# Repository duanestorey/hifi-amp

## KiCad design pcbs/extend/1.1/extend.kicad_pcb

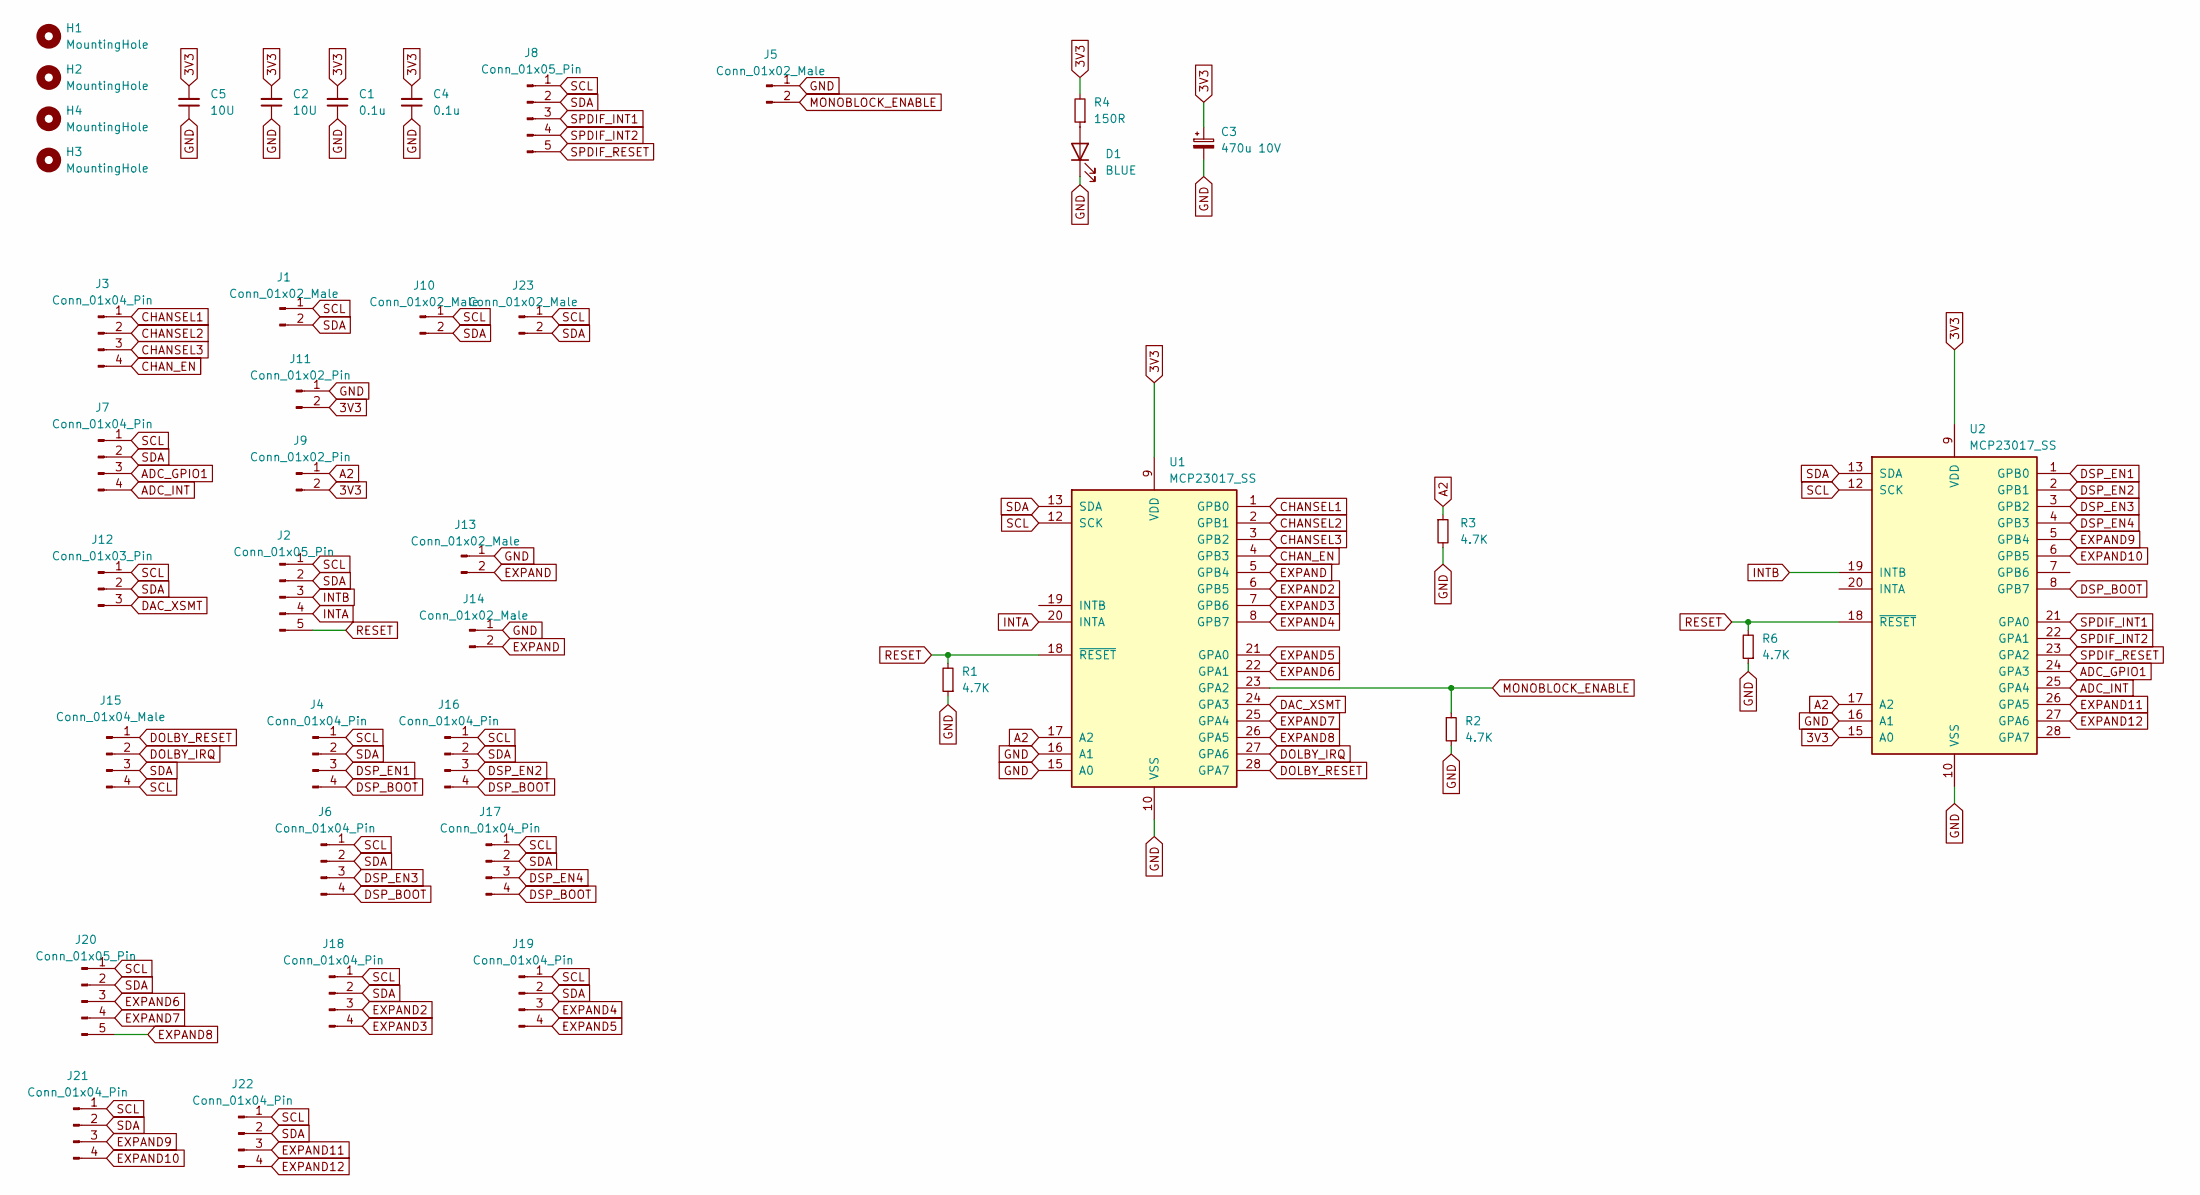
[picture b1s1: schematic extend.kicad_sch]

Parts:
C1, C4: 0.1u; C_0805_2012Metric_Pad1.18x1.45mm_HandSolder
C2, C5: 10U; C_1206_3216Metric_Pad1.33x1.80mm_HandSolder
C3: 470u 10V; CP_Radial_D6.3mm_P2.50mm
D1: BLUE; LED_0603_1608Metric
H1, H2, H3, H4: MountingHole; MountingHole_3.2mm_M3_DIN965_Pad_TopOnly
J1, J5, J10, J13, J23: Conn_01x02_Male; JST_PH_B2B-PH-K_1x02_P2.00mm_Vertical
J2, J8, J20: Conn_01x05_Pin; JST_PH_B5B-PH-K_1x05_P2.00mm_Vertical
J3, J4, J6, J7, J16, J17, J18, J19, J21, J22: Conn_01x04_Pin; JST_PH_B4B-PH-K_1x04_P2.00mm_Vertical
J9: Conn_01x02_Pin; PinHeader_1x02_P2.54mm_Vertical
J11: Conn_01x02_Pin; JST_PH_B2B-PH-K_1x02_P2.00mm_Vertical
J12: Conn_01x03_Pin; JST_PH_B3B-PH-K_1x03_P2.00mm_Vertical
J14: Conn_01x02_Male; PinHeader_1x02_P2.54mm_Vertical
J15: Conn_01x04_Male; JST_PH_B4B-PH-K_1x04_P2.00mm_Vertical
R1, R2, R3, R6: 4.7K; R_0603_1608Metric_Pad0.98x0.95mm_HandSolder
R4: 150R; R_0603_1608Metric
U1, U2: MCP23017_SS; SSOP-28_5.3x10.2mm_P0.65mm; Mouser 579-MCP23017-E/SS

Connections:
3V3: C1.2, C2.2, C3.1, C4.2, C5.2, J9.2, J11.2, R4.2, U1.9 (VDD), U2.9 (VDD), U2.15 (A0)
A2: J9.1, R3.1, U1.17 (A2), U2.17 (A2)
ADC_GPIO1: J7.3, U2.24 (GPA3)
ADC_INT: J7.4, U2.25 (GPA4)
CHANSEL1: J3.1, U1.1 (GPB0)
CHANSEL2: J3.2, U1.2 (GPB1)
CHANSEL3: J3.3, U1.3 (GPB2)
CHAN_EN: J3.4, U1.4 (GPB3)
DAC_XSMT: J12.3, U1.24 (GPA3)
DOLBY_IRQ: J15.2, U1.27 (GPA6)
DOLBY_RESET: J15.1, U1.28 (GPA7)
DSP_BOOT: J4.4, J6.4, J16.4, J17.4, U2.8 (GPB7)
DSP_EN1: J4.3, U2.1 (GPB0)
DSP_EN2: J16.3, U2.2 (GPB1)
DSP_EN3: J6.3, U2.3 (GPB2)
DSP_EN4: J17.3, U2.4 (GPB3)
EXPAND: J13.2, J14.2, U1.5 (GPB4)
EXPAND2: J18.3, U1.6 (GPB5)
EXPAND3: J18.4, U1.7 (GPB6)
EXPAND4: J19.3, U1.8 (GPB7)
EXPAND5: J19.4, U1.21 (GPA0)
EXPAND6: J20.3, U1.22 (GPA1)
EXPAND7: J20.4, U1.25 (GPA4)
EXPAND8: J20.5, U1.26 (GPA5)
EXPAND9: J21.3, U2.5 (GPB4)
EXPAND10: J21.4, U2.6 (GPB5)
EXPAND11: J22.3, U2.26 (GPA5)
EXPAND12: J22.4, U2.27 (GPA6)
GND: C1.1, C2.1, C3.2, C4.1, C5.1, D1.1 (K), J5.1, J11.1, J13.1, J14.1, R1.1, R2.1, R3.2, R6.1, U1.10 (VSS), U1.15 (A0), U1.16 (A1), U2.10 (VSS), U2.16 (A1)
INTA: J2.4, U1.20 (INTA)
INTB: J2.3, U2.19 (INTB)
MONOBLOCK_ENABLE: J5.2, R2.2, U1.23 (GPA2)
unnamed: D1.2 (A), R4.1
RESET: J2.5, R1.2, R6.2, U1.18 (~RESET), U2.18 (~RESET)
SCL: J1.1, J2.1, J4.1, J6.1, J7.1, J8.1, J10.1, J12.1, J15.4, J16.1, J17.1, J18.1, J19.1, J20.1, J21.1, J22.1, J23.1, U1.12 (SCK), U2.12 (SCK)
SDA: J1.2, J2.2, J4.2, J6.2, J7.2, J8.2, J10.2, J12.2, J15.3, J16.2, J17.2, J18.2, J19.2, J20.2, J21.2, J22.2, J23.2, U1.13 (SDA), U2.13 (SDA)
SPDIF_INT1: J8.3, U2.21 (GPA0)
SPDIF_INT2: J8.4, U2.22 (GPA1)
SPDIF_RESET: J8.5, U2.23 (GPA2)

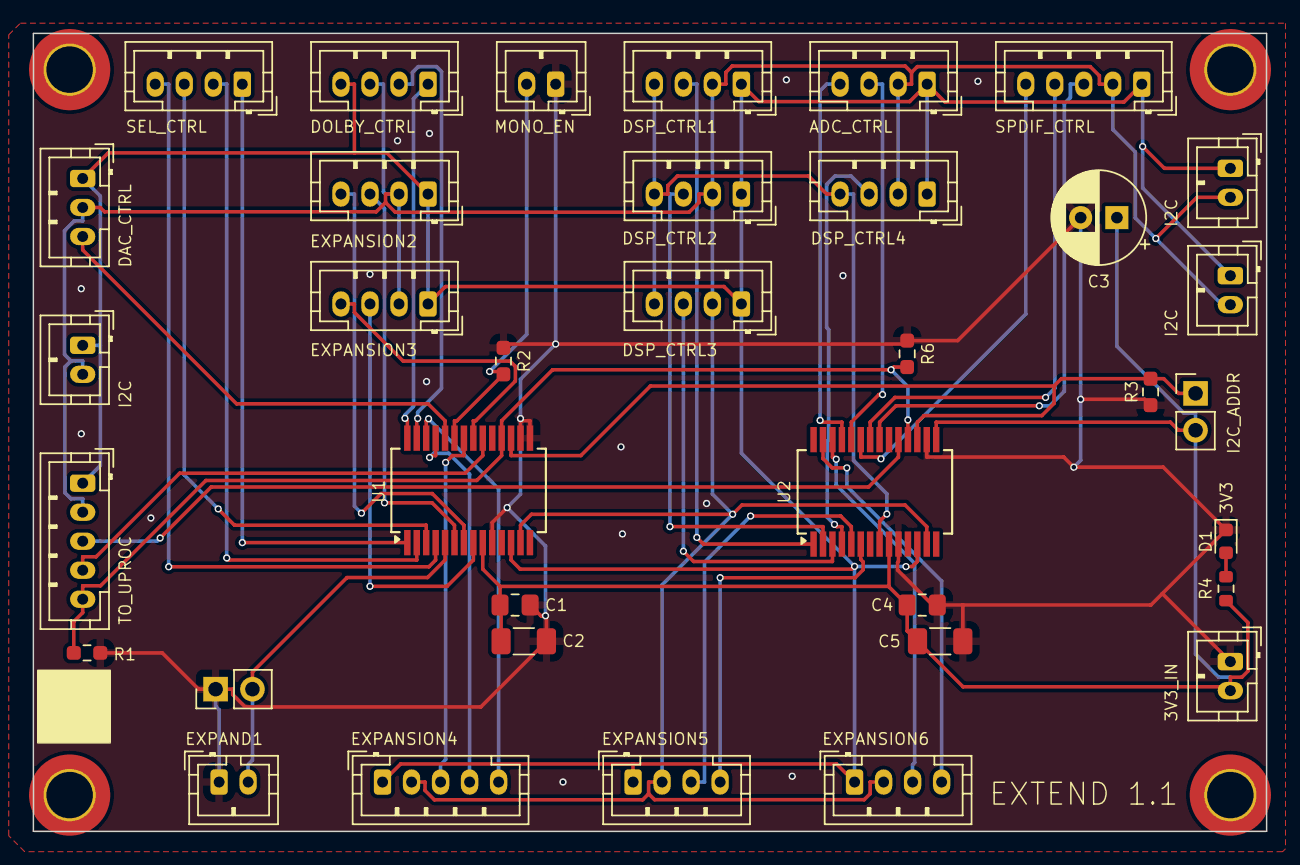
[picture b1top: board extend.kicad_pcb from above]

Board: 2 copper layers, 85.0 x 55.0 mm, 40 parts (0 on the bottom side), 39 nets.

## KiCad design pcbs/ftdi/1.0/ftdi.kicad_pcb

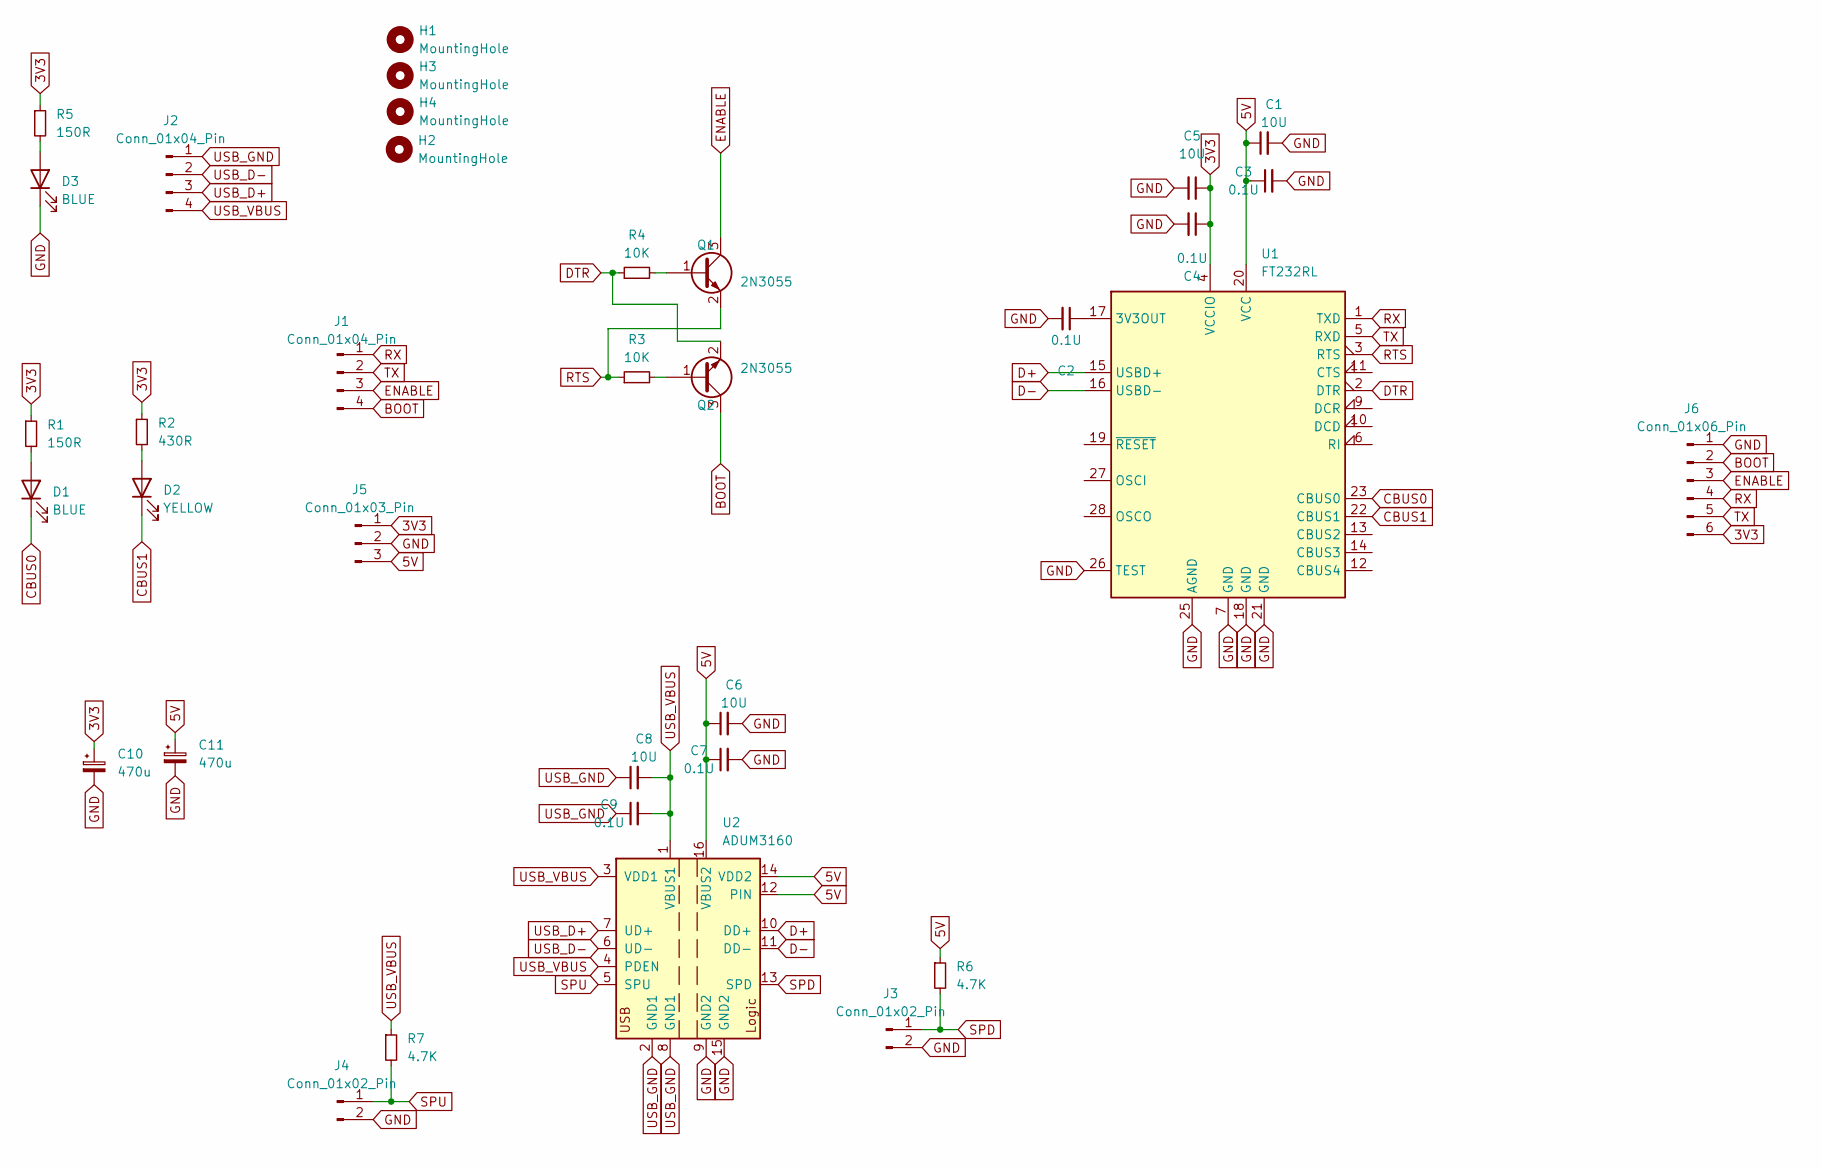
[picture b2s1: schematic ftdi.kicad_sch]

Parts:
C1, C5, C6, C8: 10U; C_1206_3216Metric_Pad1.33x1.80mm_HandSolder
C2, C3, C4, C7, C9: 0.1U; C_0805_2012Metric_Pad1.18x1.45mm_HandSolder
C10, C11: 470u; CP_Radial_D6.3mm_P2.50mm
D1, D3: BLUE; LED_0603_1608Metric_Pad1.05x0.95mm_HandSolder; LCSC XL-1608UBC-04
D2: YELLOW; LED_0603_1608Metric_Pad1.05x0.95mm_HandSolder; LCSC XL-1608UBC-04
H1, H2, H3, H4: MountingHole; MountingHole_3.2mm_M3_DIN965_Pad_TopOnly
J1, J2: Conn_01x04_Pin; JST_PH_B4B-PH-K_1x04_P2.00mm_Vertical
J3, J4: Conn_01x02_Pin; PinHeader_1x02_P2.54mm_Vertical
J5: Conn_01x03_Pin; JST_PH_B3B-PH-K_1x03_P2.00mm_Vertical
J6: Conn_01x06_Pin; PinHeader_1x06_P2.54mm_Vertical
Q1, Q2: 2N3055; TSOT-23
R1, R5: 150R; R_0603_1608Metric_Pad0.98x0.95mm_HandSolder
R2: 430R; R_0603_1608Metric_Pad0.98x0.95mm_HandSolder
R3, R4: 10K; R_0603_1608Metric_Pad0.98x0.95mm_HandSolder
R6, R7: 4.7K; R_0603_1608Metric_Pad0.98x0.95mm_HandSolder
U1: FT232RL; SSOP-28_5.3x10.2mm_P0.65mm
U2: ADUM3160; SOIC-16W_7.5x10.3mm_P1.27mm; Mouser 584-ADUM3160BRWZ-R

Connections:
3V3: C4.1, C5.1, C10.1, J5.1, J6.6, R1.1, R2.1, R5.1, U1.4 (VCCIO)
5V: C1.1, C3.1, C6.1, C7.1, C11.1, J5.3, R6.1, U1.20 (VCC), U2.12 (PIN), U2.14 (VDD2), U2.16 (VBUS2)
BOOT: J1.4, J6.2, Q2.3 (C)
CBUS0: D1.1 (K), U1.23 (CBUS0)
CBUS1: D2.1 (K), U1.22 (CBUS1)
D+: U1.15 (USBD+), U2.10 (DD+)
D-: U1.16 (USBD-), U2.11 (DD-)
DTR: Q2.2 (E), R4.1, U1.2 (DTR)
ENABLE: J1.3, J6.3, Q1.3 (C)
GND: C1.2, C2.2, C3.2, C4.2, C5.2, C6.2, C7.2, C10.2, C11.2, D3.1 (K), J3.2, J4.2, J5.2, J6.1, U1.7 (GND), U1.18 (GND), U1.21 (GND), U1.25 (AGND), U1.26 (TEST), U2.9 (GND2), U2.15 (GND2)
unnamed: D1.2 (A), R1.2
unnamed: D2.2 (A), R2.2
unnamed: D3.2 (A), R5.2
unnamed: Q1.1 (B), R4.2
unnamed: Q2.1 (B), R3.2
unnamed: C2.1, U1.17 (3V3OUT)
RTS: Q1.2 (E), R3.1, U1.3 (RTS)
RX: J1.1, J6.4, U1.1 (TXD)
SPD: J3.1, R6.2, U2.13 (SPD)
SPU: J4.1, R7.2, U2.5 (SPU)
TX: J1.2, J6.5, U1.5 (RXD)
USB_D+: J2.3, U2.7 (UD+)
USB_D-: J2.2, U2.6 (UD-)
USB_GND: C8.1, C9.1, J2.1, U2.2 (GND1), U2.8 (GND1)
USB_VBUS: C8.2, C9.2, J2.4, R7.1, U2.1 (VBUS1), U2.3 (VDD1), U2.4 (PDEN)

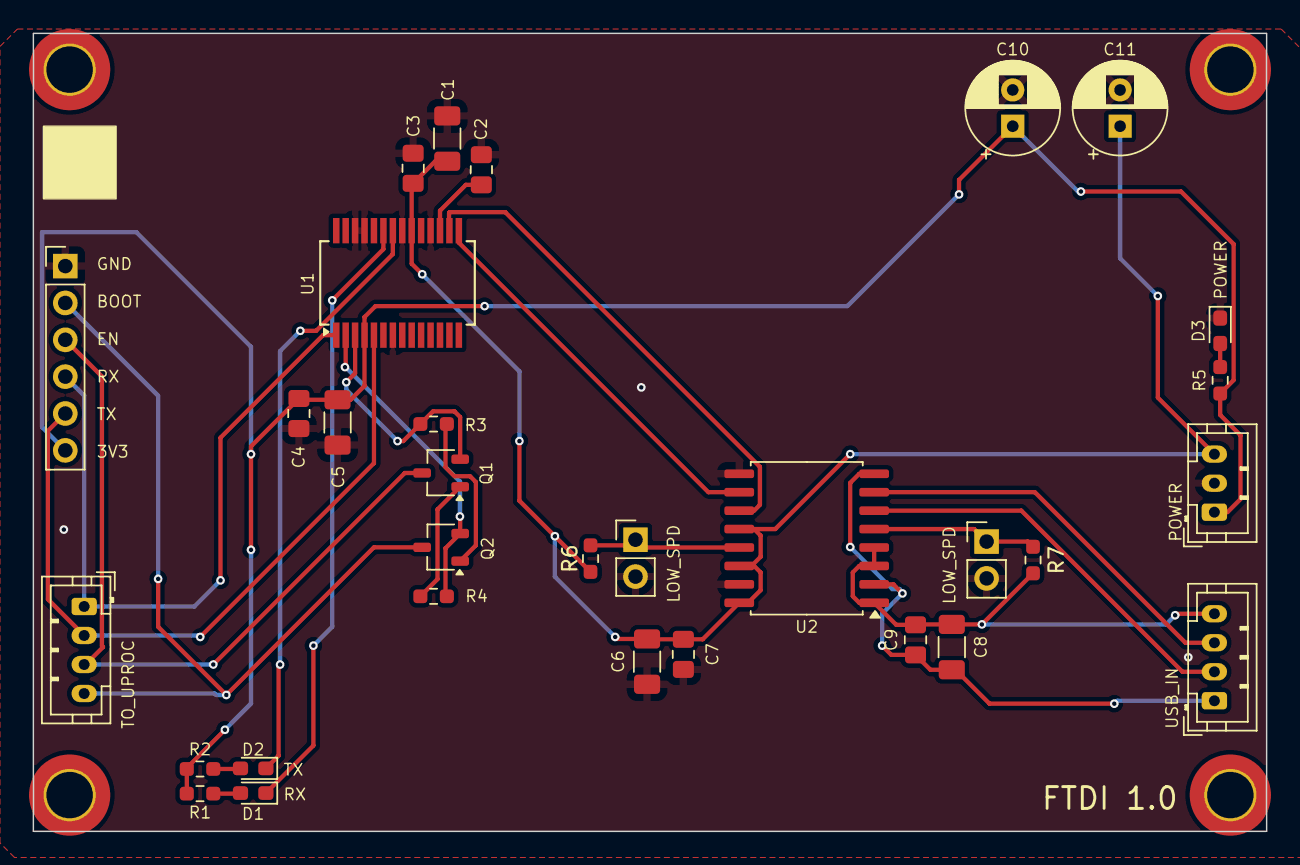
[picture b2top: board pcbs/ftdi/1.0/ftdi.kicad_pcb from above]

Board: 2 copper layers, 85.0 x 55.0 mm, 35 parts (0 on the bottom side), 25 nets.

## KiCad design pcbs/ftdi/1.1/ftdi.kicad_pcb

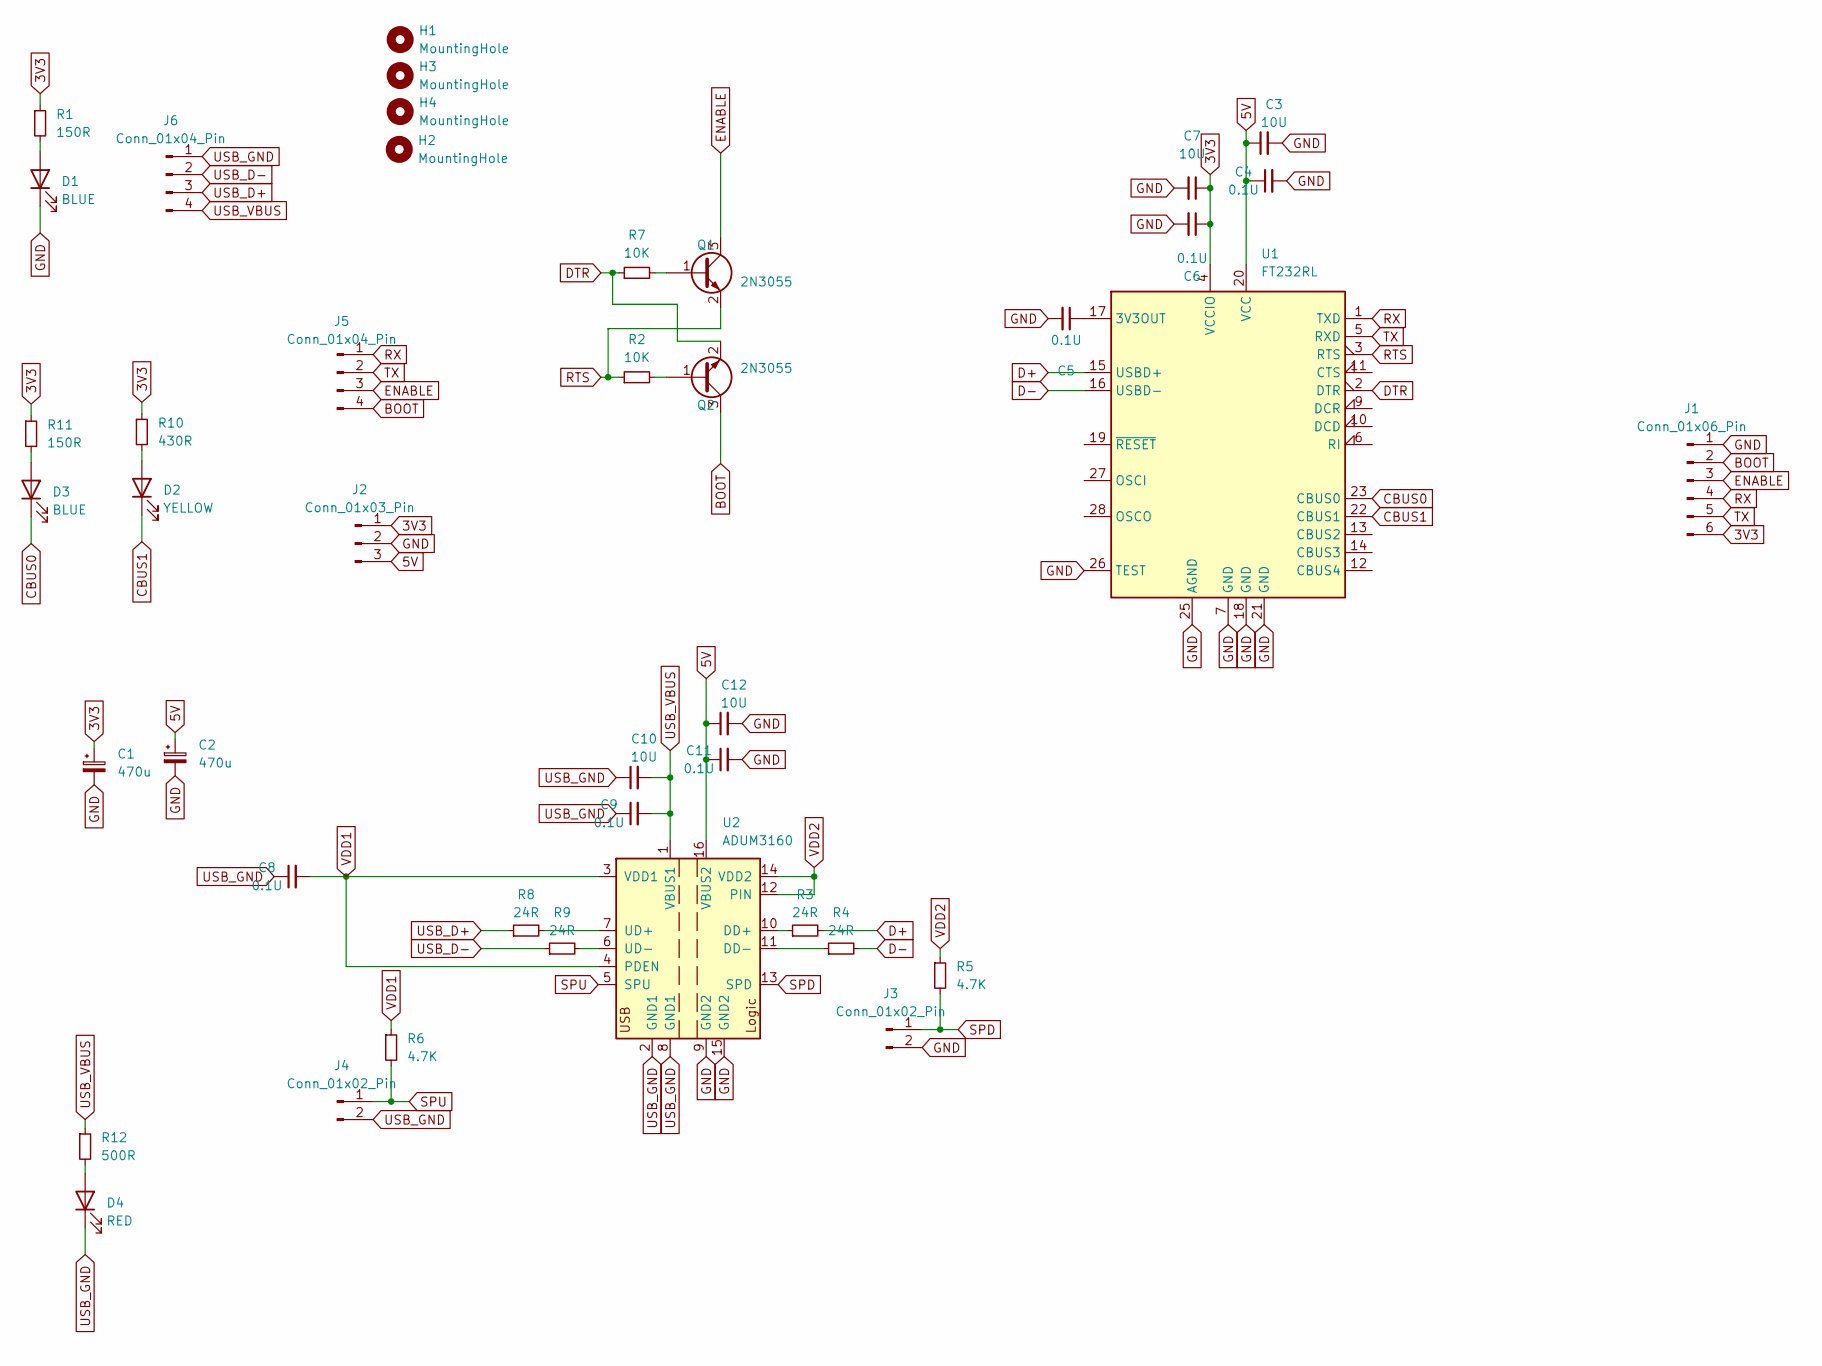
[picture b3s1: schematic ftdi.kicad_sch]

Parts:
C1, C2: 470u; CP_Radial_D6.3mm_P2.50mm
C3, C7, C10, C12: 10U; C_1206_3216Metric_Pad1.33x1.80mm_HandSolder
C4, C5, C6, C8, C9, C11: 0.1U; C_0805_2012Metric_Pad1.18x1.45mm_HandSolder
D1, D3: BLUE; LED_0603_1608Metric_Pad1.05x0.95mm_HandSolder; LCSC XL-1608UBC-04
D2: YELLOW; LED_0603_1608Metric_Pad1.05x0.95mm_HandSolder; LCSC XL-1608UBC-04
D4: RED; LED_0603_1608Metric_Pad1.05x0.95mm_HandSolder; LCSC XL-1608UBC-04
H1, H2, H3, H4: MountingHole; MountingHole_3.2mm_M3_DIN965_Pad_TopOnly
J1: Conn_01x06_Pin; PinHeader_1x06_P2.54mm_Vertical
J2: Conn_01x03_Pin; JST_PH_B3B-PH-K_1x03_P2.00mm_Vertical
J3, J4: Conn_01x02_Pin; PinHeader_1x02_P2.54mm_Vertical
J5, J6: Conn_01x04_Pin; JST_PH_B4B-PH-K_1x04_P2.00mm_Vertical
Q1, Q2: 2N3055; TSOT-23
R1, R11: 150R; R_0603_1608Metric_Pad0.98x0.95mm_HandSolder
R2, R7: 10K; R_0603_1608Metric_Pad0.98x0.95mm_HandSolder
R3, R4, R8, R9: 24R; R_0603_1608Metric_Pad0.98x0.95mm_HandSolder
R5, R6: 4.7K; R_0603_1608Metric_Pad0.98x0.95mm_HandSolder
R10: 430R; R_0603_1608Metric_Pad0.98x0.95mm_HandSolder
R12: 500R; R_0603_1608Metric_Pad0.98x0.95mm_HandSolder
U1: FT232RL; SSOP-28_5.3x10.2mm_P0.65mm
U2: ADUM3160; SOIC-16W_7.5x10.3mm_P1.27mm; Mouser 584-ADUM3160BRWZ-R

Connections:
3V3: C1.1, C6.1, C7.1, J1.6, J2.1, R1.1, R10.1, R11.1, U1.4 (VCCIO)
5V: C2.1, C3.1, C4.1, C11.1, C12.1, J2.3, U1.20 (VCC), U2.16 (VBUS2)
BOOT: J1.2, J5.4, Q2.3 (C)
CBUS0: D3.1 (K), U1.23 (CBUS0)
CBUS1: D2.1 (K), U1.22 (CBUS1)
D+: R3.2, U1.15 (USBD+)
D-: R4.2, U1.16 (USBD-)
DTR: Q2.2 (E), R7.1, U1.2 (DTR)
ENABLE: J1.3, J5.3, Q1.3 (C)
GND: C1.2, C2.2, C3.2, C4.2, C5.2, C6.2, C7.2, C11.2, C12.2, D1.1 (K), J1.1, J2.2, J3.2, U1.7 (GND), U1.18 (GND), U1.21 (GND), U1.25 (AGND), U1.26 (TEST), U2.9 (GND2), U2.15 (GND2)
unnamed: D1.2 (A), R1.2
unnamed: D2.2 (A), R10.2
unnamed: D3.2 (A), R11.2
unnamed: D4.2 (A), R12.2
unnamed: Q1.1 (B), R7.2
unnamed: Q2.1 (B), R2.2
unnamed: C5.1, U1.17 (3V3OUT)
unnamed: R3.1, U2.10 (DD+)
unnamed: R4.1, U2.11 (DD-)
unnamed: R8.2, U2.7 (UD+)
unnamed: R9.2, U2.6 (UD-)
RTS: Q1.2 (E), R2.1, U1.3 (RTS)
RX: J1.4, J5.1, U1.1 (TXD)
SPD: J3.1, R5.2, U2.13 (SPD)
SPU: J4.1, R6.2, U2.5 (SPU)
TX: J1.5, J5.2, U1.5 (RXD)
USB_D+: J6.3, R8.1
USB_D-: J6.2, R9.1
USB_GND: C8.1, C9.1, C10.1, D4.1 (K), J4.2, J6.1, U2.2 (GND1), U2.8 (GND1)
USB_VBUS: C9.2, C10.2, J6.4, R12.1, U2.1 (VBUS1)
VDD1: C8.2, R6.1, U2.3 (VDD1), U2.4 (PDEN)
VDD2: R5.1, U2.12 (PIN), U2.14 (VDD2)

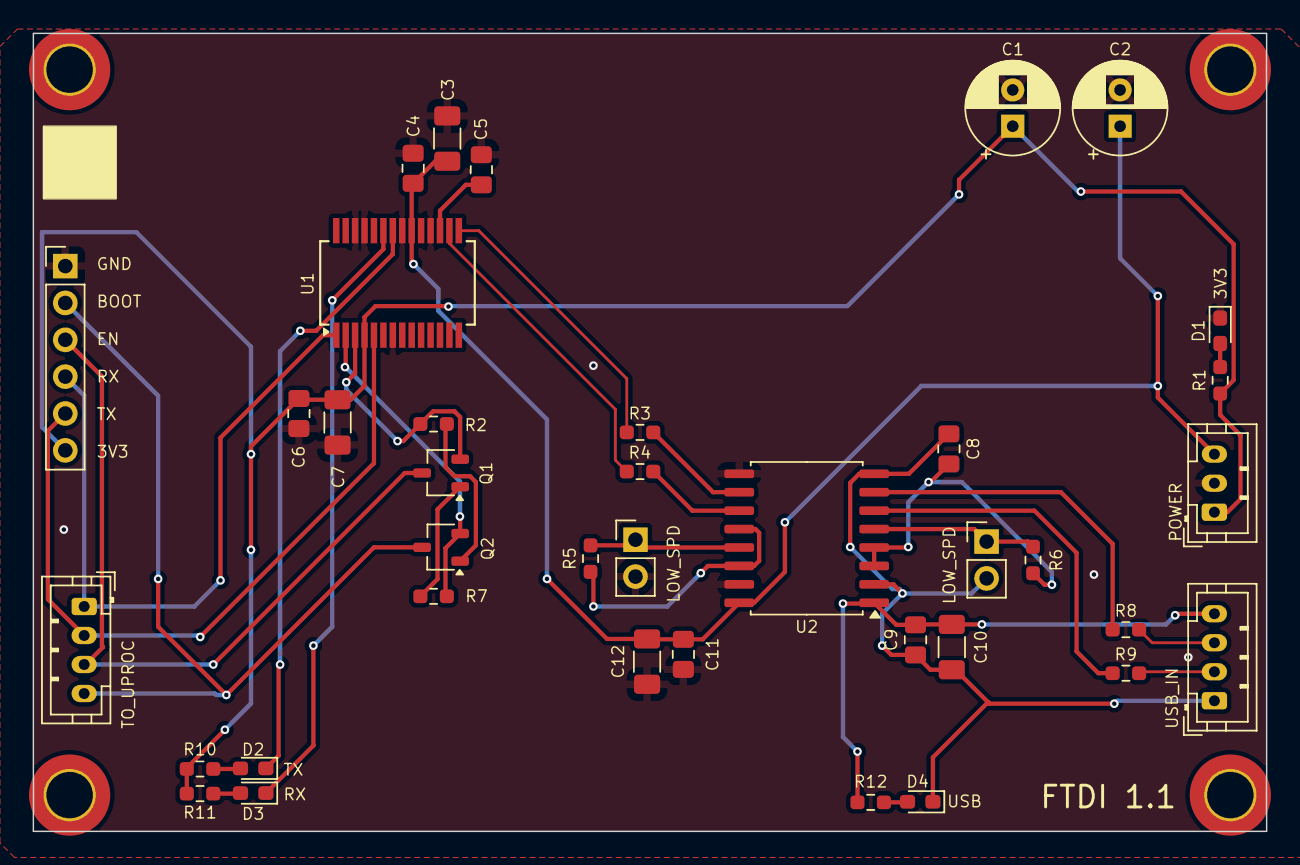
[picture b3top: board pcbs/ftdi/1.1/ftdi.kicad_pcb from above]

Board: 2 copper layers, 85.0 x 55.0 mm, 42 parts (0 on the bottom side), 32 nets.

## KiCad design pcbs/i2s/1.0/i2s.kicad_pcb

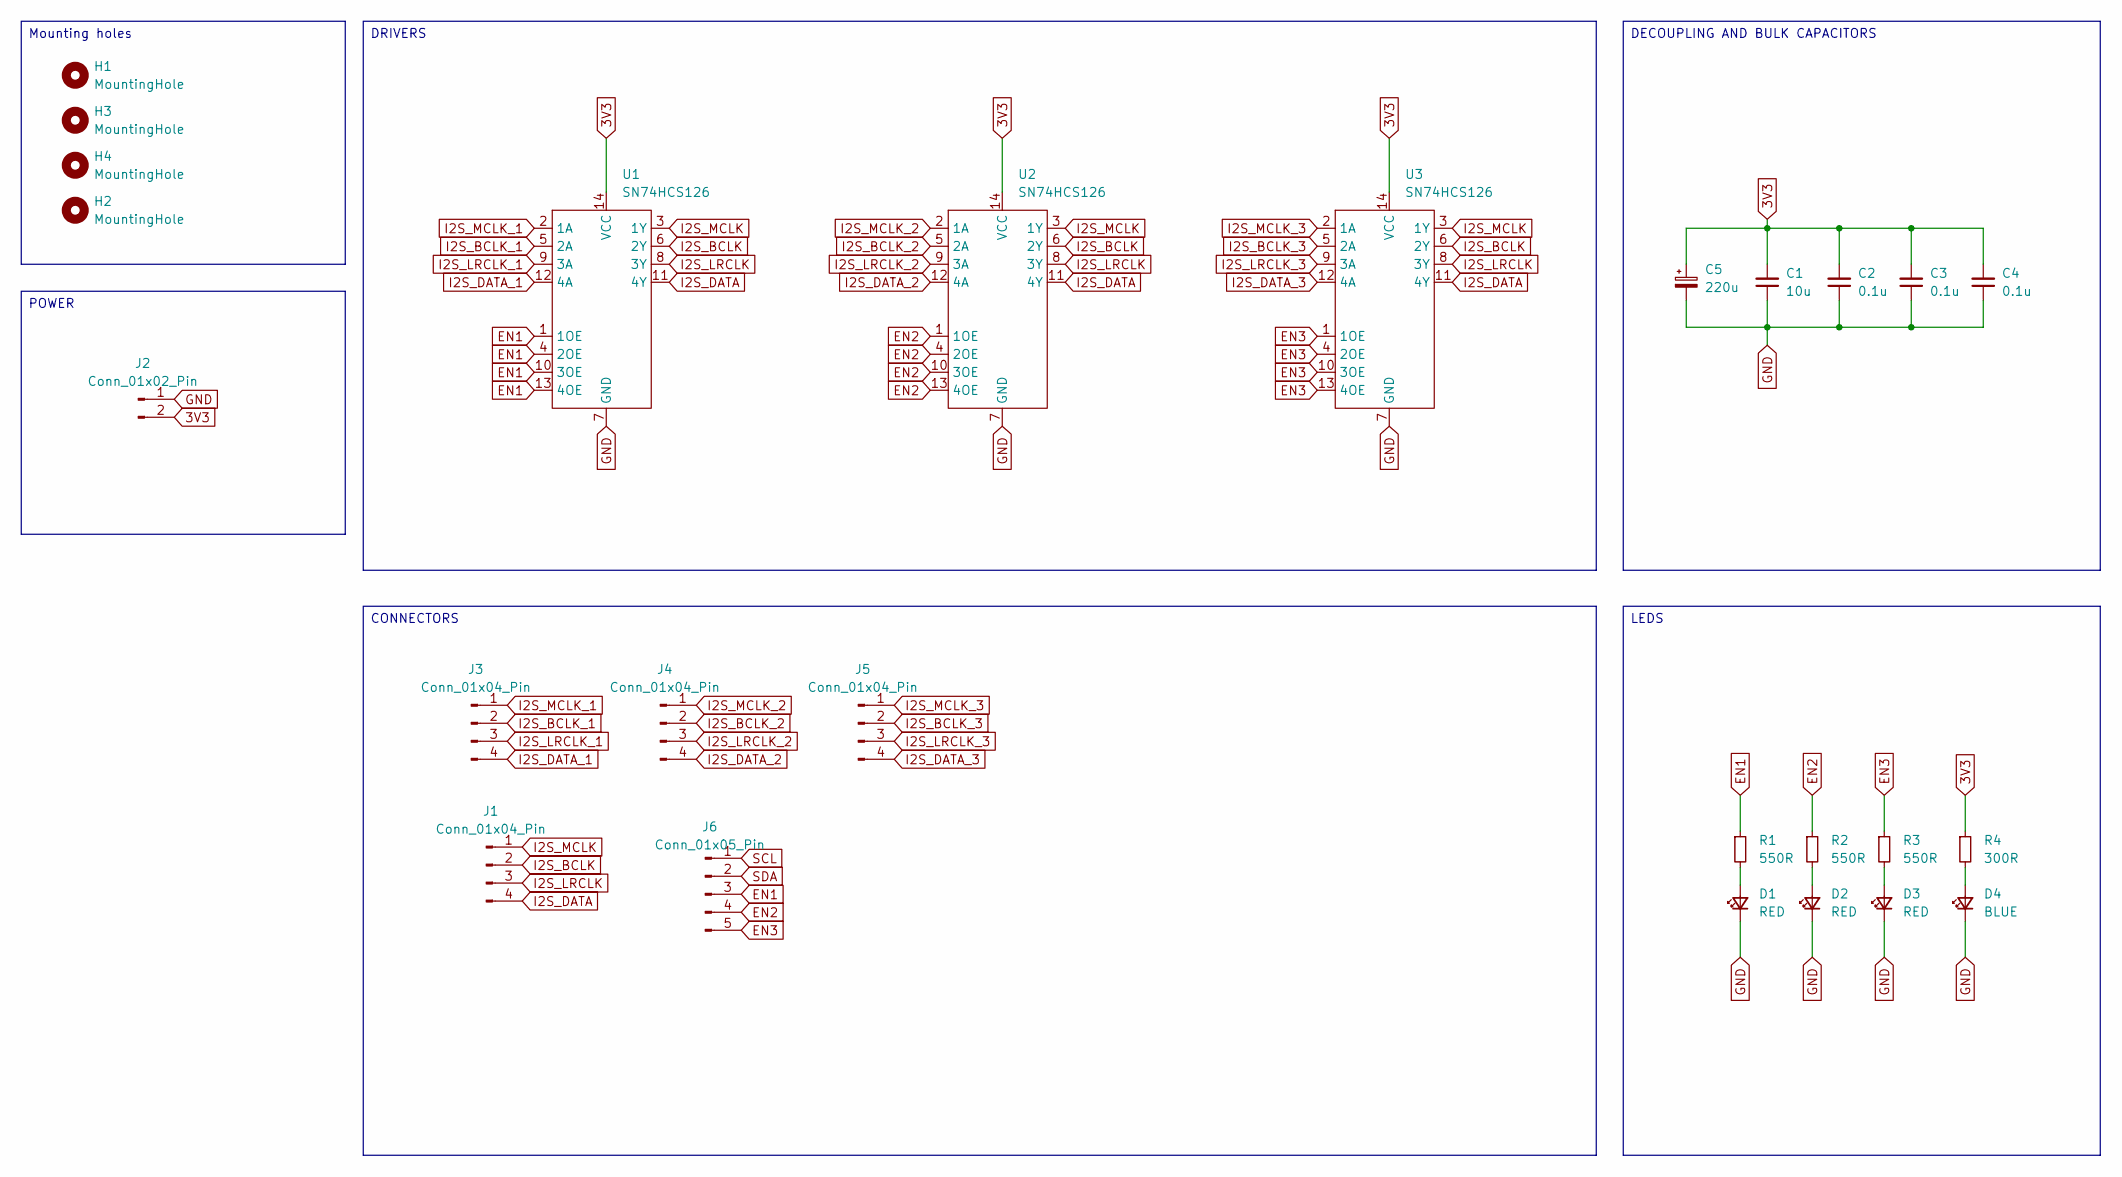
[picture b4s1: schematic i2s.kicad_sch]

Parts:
C1: 10u; C_1206_3216Metric_Pad1.33x1.80mm_HandSolder
C2, C3, C4: 0.1u; C_0805_2012Metric_Pad1.18x1.45mm_HandSolder
C5: 220u; CP_Radial_D6.3mm_P2.50mm
D1, D2, D3: RED; LED_0805_2012Metric_Pad1.15x1.40mm_HandSolder
D4: BLUE; LED_0805_2012Metric_Pad1.15x1.40mm_HandSolder
H1, H2, H3, H4: MountingHole; MountingHole_3.2mm_M3_DIN965_Pad_TopBottom
J1, J3, J4, J5: Conn_01x04_Pin; JST_PH_B4B-PH-K_1x04_P2.00mm_Vertical
J2: Conn_01x02_Pin; JST_PH_B2B-PH-K_1x02_P2.00mm_Vertical
J6: Conn_01x05_Pin; JST_PH_B5B-PH-K_1x05_P2.00mm_Vertical
R1, R2, R3: 550R; R_0603_1608Metric_Pad0.98x0.95mm_HandSolder
R4: 300R; R_0603_1608Metric_Pad0.98x0.95mm_HandSolder
U1, U2, U3: SN74HCS126; TSSOP-14_4.4x5mm_P0.65mm

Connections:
3V3: C1.2, C2.2, C3.2, C4.2, C5.1, J2.2, R4.1, U1.14 (VCC), U2.14 (VCC), U3.14 (VCC)
EN1: J6.3, R1.1, U1.1 (1OE), U1.4 (2OE), U1.10 (3OE), U1.13 (4OE)
EN2: J6.4, R2.1, U2.1 (1OE), U2.4 (2OE), U2.10 (3OE), U2.13 (4OE)
EN3: J6.5, R3.1, U3.1 (1OE), U3.4 (2OE), U3.10 (3OE), U3.13 (4OE)
GND: C1.1, C2.1, C3.1, C4.1, C5.2, D1.1 (K), D2.1 (K), D3.1 (K), D4.1 (K), J2.1, U1.7 (GND), U2.7 (GND), U3.7 (GND)
I2S_BCLK: J1.2, U1.6 (2Y), U2.6 (2Y), U3.6 (2Y)
I2S_BCLK_1: J3.2, U1.5 (2A)
I2S_BCLK_2: J4.2, U2.5 (2A)
I2S_BCLK_3: J5.2, U3.5 (2A)
I2S_DATA: J1.4, U1.11 (4Y), U2.11 (4Y), U3.11 (4Y)
I2S_DATA_1: J3.4, U1.12 (4A)
I2S_DATA_2: J4.4, U2.12 (4A)
I2S_DATA_3: J5.4, U3.12 (4A)
I2S_LRCLK: J1.3, U1.8 (3Y), U2.8 (3Y), U3.8 (3Y)
I2S_LRCLK_1: J3.3, U1.9 (3A)
I2S_LRCLK_2: J4.3, U2.9 (3A)
I2S_LRCLK_3: J5.3, U3.9 (3A)
I2S_MCLK: J1.1, U1.3 (1Y), U2.3 (1Y), U3.3 (1Y)
I2S_MCLK_1: J3.1, U1.2 (1A)
I2S_MCLK_2: J4.1, U2.2 (1A)
I2S_MCLK_3: J5.1, U3.2 (1A)
unnamed: D1.2 (A), R1.2
unnamed: D2.2 (A), R2.2
unnamed: D3.2 (A), R3.2
unnamed: D4.2 (A), R4.2
SCL: J6.1
SDA: J6.2

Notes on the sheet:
DRIVERS
DECOUPLING AND BULK CAPACITORS
Mounting holes
LEDS
POWER
CONNECTORS

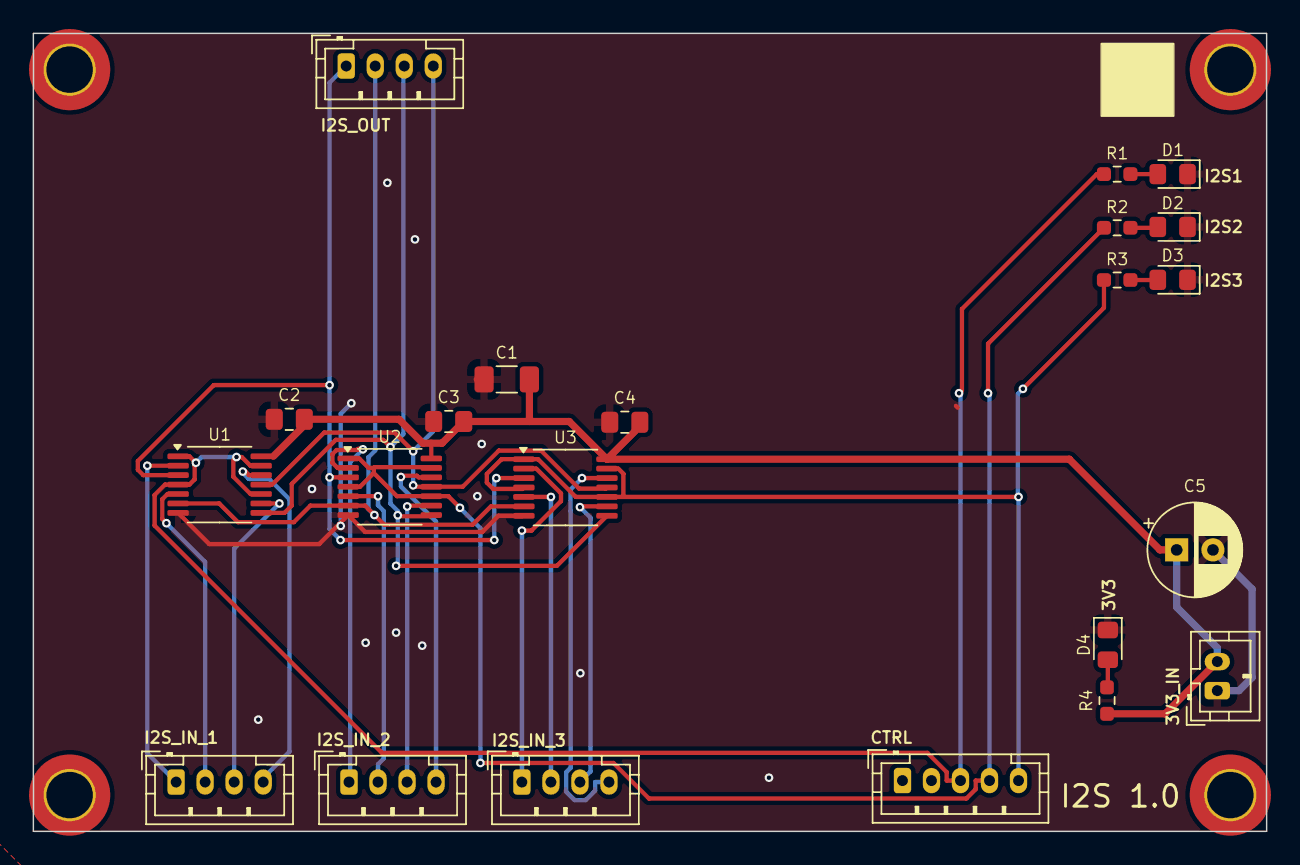
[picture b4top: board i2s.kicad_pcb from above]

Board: 2 copper layers, 85.0 x 55.0 mm, 26 parts (0 on the bottom side), 25 nets.

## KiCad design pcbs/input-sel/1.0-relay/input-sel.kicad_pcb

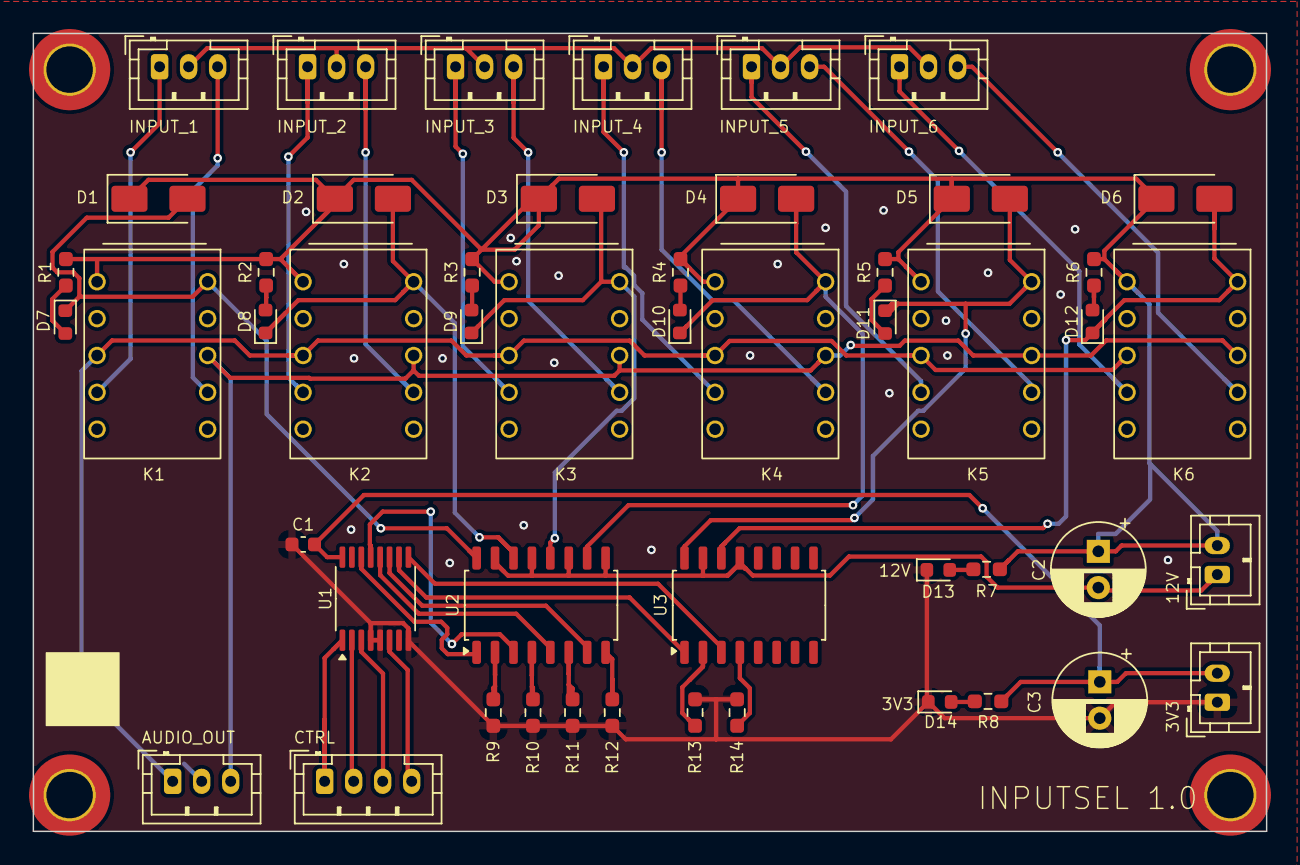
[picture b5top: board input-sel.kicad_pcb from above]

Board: 2 copper layers, 85.0 x 55.0 mm, 54 parts (0 on the bottom side), 49 nets.

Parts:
C1: 0.1u; C_0603_1608Metric
C2, C3: 470u; CP_Radial_D6.3mm_P2.50mm
D1, D2, D3, D4, D5, D6: D; D_SMA
D7, D8, D9, D10, D11, D12, D13: RED; LED_0603_1608Metric
D14: BLUE; LED_0603_1608Metric
H1, H2, H3, H4: MountingHole; MountingHole_3.2mm_M3_DIN965_Pad_TopOnly
J1, J2, J3, J4, J5, J6, J9: Conn_01x03_Pin; JST_PH_B3B-PH-K_1x03_P2.00mm_Vertical
J7, J8: Conn_01x02_Pin; JST_PH_B2B-PH-K_1x02_P2.00mm_Vertical
J10: Conn_01x04_Pin; JST_PH_B4B-PH-K_1x04_P2.00mm_Vertical
K1, K2, K3, K4, K5, K6: EC2-5NU; KEMET EA2
R1, R2, R3, R4, R5, R6: 4.7K; R_0603_1608Metric_Pad0.98x0.95mm_HandSolder
R7: 75R; R_0603_1608Metric_Pad0.98x0.95mm_HandSolder
R8: 150R; R_0603_1608Metric_Pad0.98x0.95mm_HandSolder
R9, R10, R11, R12, R13, R14: 820R; R_0603_1608Metric_Pad0.98x0.95mm_HandSolder
U1: CD74AC238; TSSOP-16_4.4x5mm_P0.65mm
U2, U3: TCMT4600; SOP-16_4.55x10.3mm_P1.27mm

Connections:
3V3: C1.1, C3.1, J8.2, R8.2, U1.16 (VCC)
12V: C2.1, D1.1 (K), D2.1 (K), D3.1 (K), D4.1 (K), D5.1 (K), D6.1 (K), J7.2, K1.1, K2.1, K3.1, K4.1, K5.1, K6.1, R1.2, R2.2, R3.2, R4.2, R5.2, R6.2, R7.2
AGND: J1.2, J2.2, J3.2, J4.2, J5.2, J6.2, J9.2
CTRL1: J10.1, U1.1 (A0)
CTRL2: J10.2, U1.2 (A1)
CTRL3: J10.3, U1.3 (A2)
EN: J10.4, U1.6 (E3)
GND: C1.2, C3.2, D13.1 (K), D14.1 (K), J8.1, R9.2, R10.2, R11.2, R12.2, R13.2, R14.2, U1.4 (~E1), U1.5 (~E2), U1.8 (GND)
unnamed: D1.2 (A), D7.1 (K), K1.12, U2.16
unnamed: D2.2 (A), D8.1 (K), K2.12, U2.14
unnamed: D3.2 (A), D9.1 (K), K3.12, U2.12
unnamed: D7.2 (A), R1.1
unnamed: D8.2 (A), R2.1
unnamed: D9.2 (A), R3.1
unnamed: D10.2 (A), R4.1
unnamed: D4.2 (A), D10.1 (K), K4.12, U2.10
unnamed: D11.2 (A), R5.1
unnamed: D5.2 (A), D11.1 (K), K5.12, U3.16
unnamed: D12.2 (A), R6.1
unnamed: D6.2 (A), D12.1 (K), K6.12, U3.14
unnamed: D13.2 (A), R7.1
unnamed: D14.2 (A), R8.1
unnamed: R9.1, U2.2
unnamed: R10.1, U2.4
unnamed: R11.1, U2.6
unnamed: R12.1, U2.8
unnamed: R13.1, U3.2
unnamed: R14.1, U3.4
OUT_L: J9.1, K1.4, K2.4, K3.4, K4.4, K5.4, K6.4
OUT_R: J9.3, K1.9, K2.9, K3.9, K4.9, K5.9, K6.9
RCA1_L: J1.1, K1.5
RCA1_R: J1.3, K1.8
RCA2_L: J2.1, K2.5
RCA2_R: J2.3, K2.8
RCA3_L: J3.1, K3.5
RCA3_R: J3.3, K3.8
RCA4_L: J4.1, K4.5
RCA4_R: J4.3, K4.8
RCA5_L: J5.1, K5.5
RCA5_R: J5.3, K5.8
RCA6_L: J6.1, K6.5
RCA6_R: J6.3, K6.8
RELAY1: U1.14 (Y1), U2.1
RELAY2: U1.13 (Y2), U2.3
RELAY3: U1.12 (Y3), U2.5
RELAY4: U1.11 (Y4), U2.7
RELAY5: U1.10 (Y5), U3.1
RELAY6: U1.9 (Y6), U3.3
RELAY_GND: C2.2, J7.1, U2.9, U2.11, U2.13, U2.15, U3.13, U3.15
